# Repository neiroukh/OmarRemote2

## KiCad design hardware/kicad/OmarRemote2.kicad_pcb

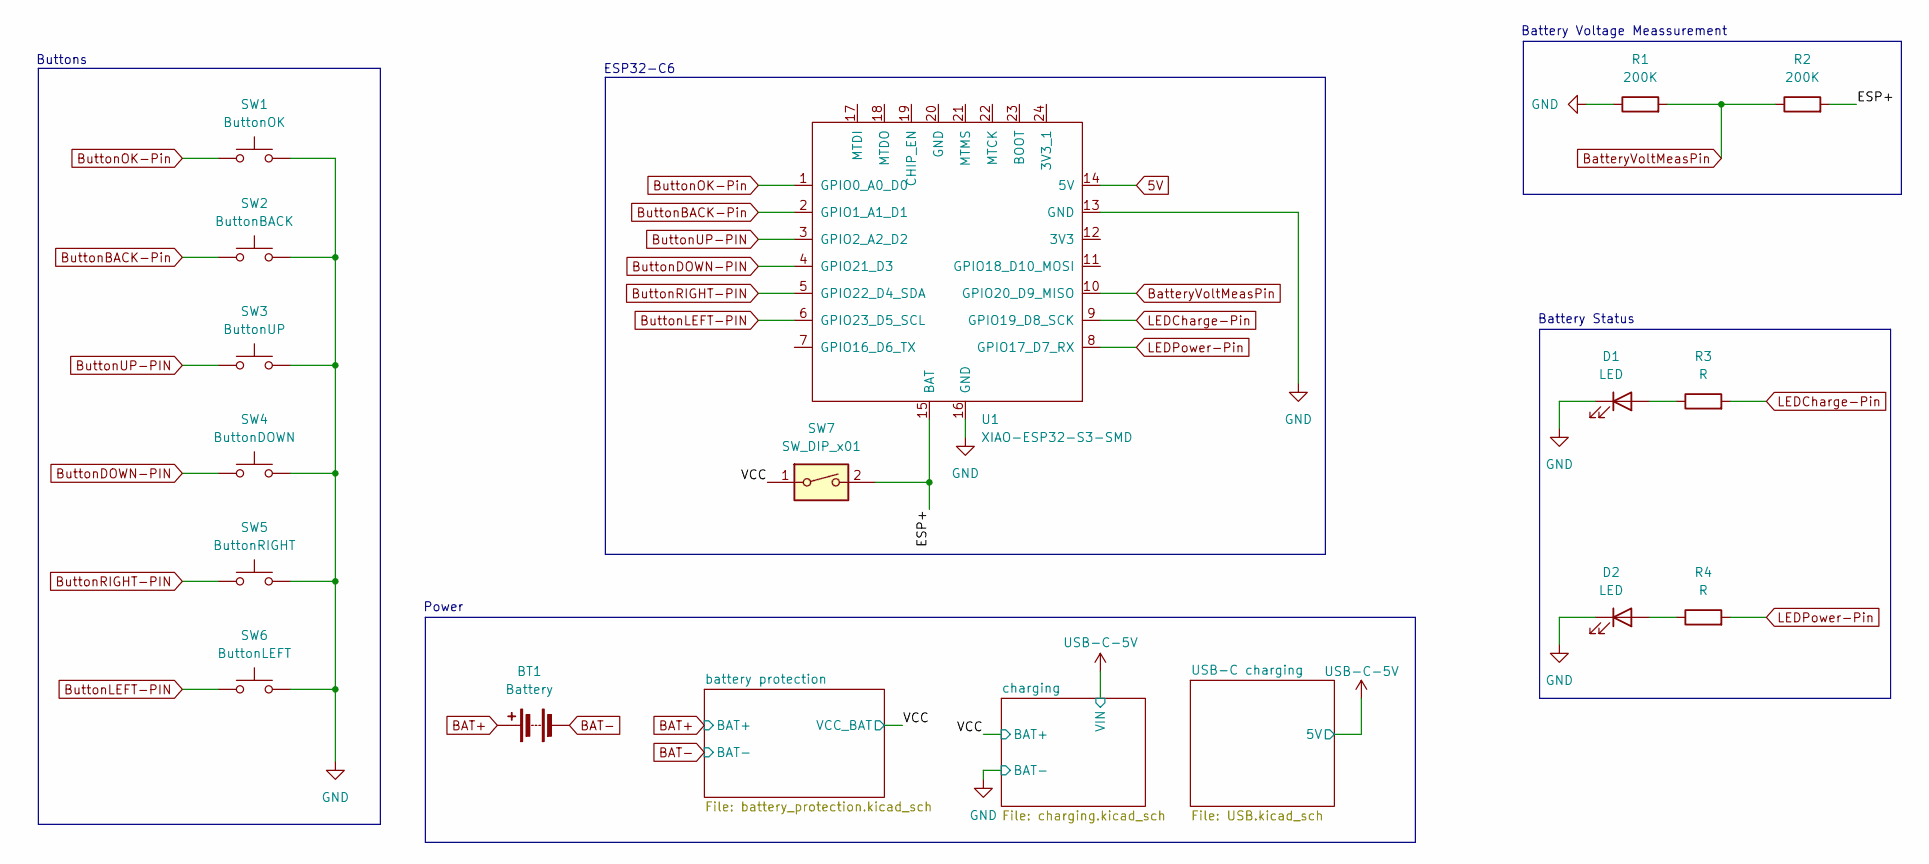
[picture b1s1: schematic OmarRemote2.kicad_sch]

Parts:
BT1: Battery; BatteryHolder_Keystone_1042_1x18650
D1, D2: LED; JST_XH_B2B-XH-A_1x02_P2.50mm_Vertical
R1, R2: 200K; R_0805_2012Metric
R3, R4: R; R_0805_2012Metric
SW1: ButtonOK; SW-TH_4P-L6.0-W6.0-P4.50-LS6.5
SW2: ButtonBACK; SW-TH_4P-L6.0-W6.0-P4.50-LS6.5
SW3: ButtonUP; SW-TH_4P-L6.0-W6.0-P4.50-LS6.5
SW4: ButtonDOWN; SW-TH_4P-L6.0-W6.0-P4.50-LS6.5
SW5: ButtonRIGHT; SW-TH_4P-L6.0-W6.0-P4.50-LS6.5
SW6: ButtonLEFT; SW-TH_4P-L6.0-W6.0-P4.50-LS6.5
SW7: SW_DIP_x01; JST_XH_B2B-XH-AM_1x02_P2.50mm_Vertical
U1: XIAO-ESP32-S3-SMD; XIAO-ESP32C6-SMD

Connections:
5V: U1.14 (5V); also elsewhere on the board
/ESP+: R2.2, SW7.2, U1.15 (BAT)
BAT+: BT1.1 (+), SW7.1; also elsewhere on the board
BAT-: BT1.2 (-); also elsewhere on the board
BatteryVoltMeasPin: R1.2, R2.1, U1.10 (GPIO20_D9_MISO)
ButtonBACK-Pin: SW2.1, U1.2 (GPIO1_A1_D1)
ButtonDOWN-PIN: SW4.1, U1.4 (GPIO21_D3)
ButtonLEFT-PIN: SW6.1, U1.6 (GPIO23_D5_SCL)
ButtonOK-Pin: SW1.1, U1.1 (GPIO0_A0_D0)
ButtonRIGHT-PIN: SW5.1, U1.5 (GPIO22_D4_SDA)
ButtonUP-PIN: SW3.1, U1.3 (GPIO2_A2_D2)
GND: D1.1 (K), D2.1 (K), R1.1, SW1.2, SW2.2, SW3.2, SW4.2, SW5.2, SW6.2, U1.13 (GND), U1.16 (GND); also elsewhere on the board
LEDCharge-Pin: R3.2, U1.9 (GPIO19_D8_SCK)
LEDPower-Pin: R4.2, U1.8 (GPIO17_D7_RX)
unnamed: D1.2 (A), R3.1
unnamed: D2.2 (A), R4.1

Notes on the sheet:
ESP32-C6
Battery Status
Power
Battery Voltage Meassurement
Buttons

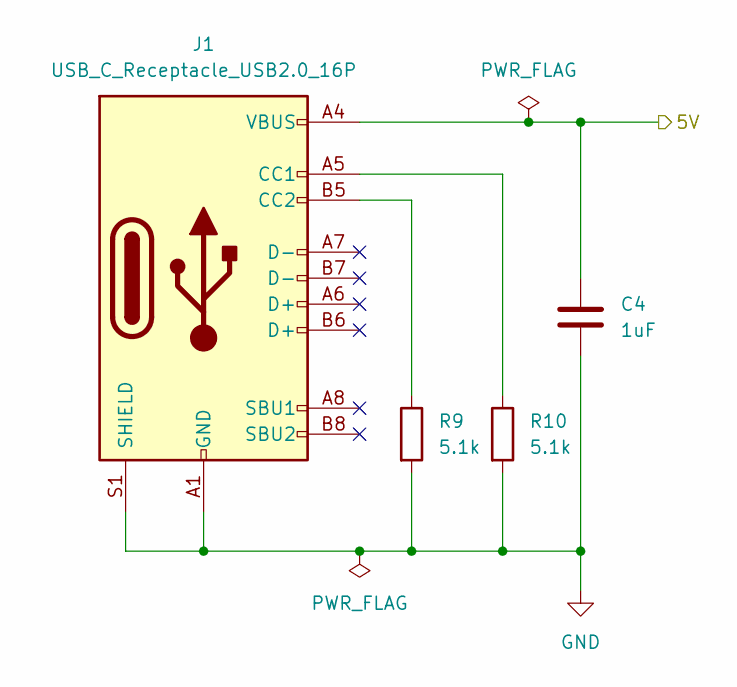
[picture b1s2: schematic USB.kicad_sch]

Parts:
C4: 1uF; C_0603_1608Metric_Pad1.08x0.95mm_HandSolder; LCSC C15849
J1: USB_C_Receptacle_USB2.0_16P; USB_C_Receptacle_G-Switch_GT-USB-7010ASV; LCSC C2988369
R9, R10: 5.1k; R_0603_1608Metric_Pad0.98x0.95mm_HandSolder; LCSC C23186

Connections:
GND: C4.2, J1.A1 (GND), J1.A12 (GND), J1.B1 (GND), J1.B12 (GND), J1.S1 (SHIELD), R9.2, R10.2; also elsewhere on the board
unnamed: J1.A5 (CC1), R10.1
unnamed: J1.B5 (CC2), R9.1
USB-C-5V: C4.1, J1.A4 (VBUS), J1.A9 (VBUS), J1.B4 (VBUS), J1.B9 (VBUS); also elsewhere on the board

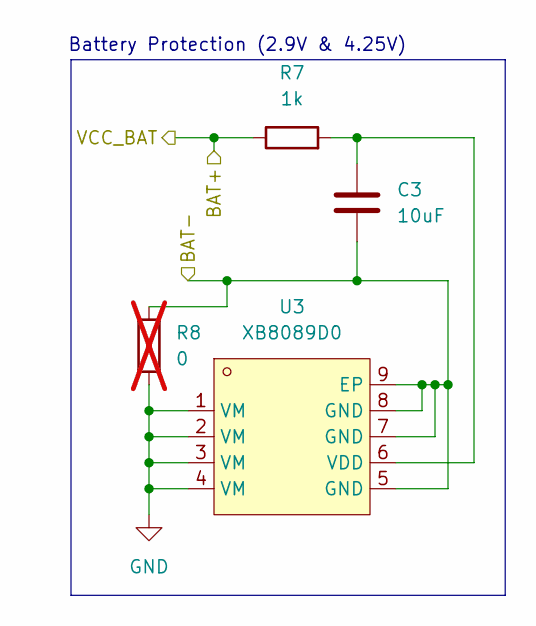
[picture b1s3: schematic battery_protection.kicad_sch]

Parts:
C3: 10uF; C_0603_1608Metric_Pad1.08x0.95mm_HandSolder; LCSC C19702
R7: 1k; R_0603_1608Metric_Pad0.98x0.95mm_HandSolder; LCSC C21190
R8: 0; R_0603_1608Metric_Pad0.98x0.95mm_HandSolder; LCSC C21189; not fitted
U3: XB8089D0; HTSOP-8-1EP_3.9x4.9mm_P1.27mm_EP2.4x3.2mm; LCSC C2760005

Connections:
BAT+: R7.1; also elsewhere on the board
BAT-: C3.2, R8.1, U3.5 (GND), U3.7 (GND), U3.8 (GND), U3.9 (EP); also elsewhere on the board
GND: R8.2, U3.1 (VM), U3.2 (VM), U3.3 (VM), U3.4 (VM); also elsewhere on the board
unnamed: C3.1, R7.2, U3.6 (VDD)

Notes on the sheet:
Battery Protection (2.9V & 4.25V)

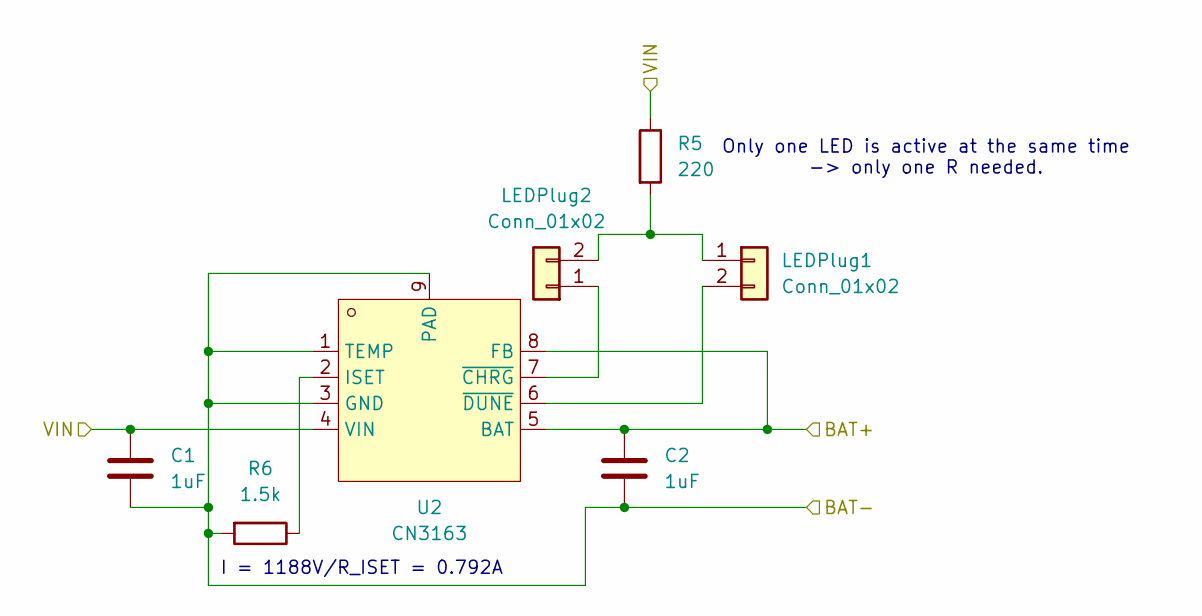
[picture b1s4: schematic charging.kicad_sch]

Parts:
C1, C2: 1uF; C_0603_1608Metric_Pad1.08x0.95mm_HandSolder; LCSC C15849
LEDPlug1, LEDPlug2: Conn_01x02; JST_XH_B2B-XH-A_1x02_P2.50mm_Vertical
R5: 220; R_0603_1608Metric_Pad0.98x0.95mm_HandSolder; LCSC C21190
R6: 1.5k; R_0603_1608Metric_Pad0.98x0.95mm_HandSolder
U2: CN3163; ESOP-8_L4.9-W3.9-P1.27-LS6.0-BL-EP; LCSC Part C559031

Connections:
BAT+: C2.1, U2.5 (BAT), U2.8 (FB); also elsewhere on the board
GND: C1.2, C2.2, R6.2, U2.1 (TEMP), U2.3 (GND), U2.9 (PAD); also elsewhere on the board
unnamed: LEDPlug1.1, LEDPlug2.2, R5.2
unnamed: LEDPlug1.2, U2.6 (~DUNE)
unnamed: LEDPlug2.1, U2.7 (~CHRG)
unnamed: R6.1, U2.2 (ISET)
USB-C-5V: C1.1, R5.1, U2.4 (VIN); also elsewhere on the board

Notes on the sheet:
Only one LED is active at the same time -> only one R needed.
I = 1188V/R_ISET = 0.792A

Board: 2 copper layers, 31 parts (0 on the bottom side), 24 nets, no tracks yet.

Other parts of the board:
J2: Conn_01x03; JST_XH_B3B-XH-A_1x03_P2.50mm_Vertical

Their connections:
5V: J2.2; also elsewhere on the board
GND: J2.3; also elsewhere on the board

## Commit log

2026-02-28 chore: update main gitignore
2026-03-02 feat: add basic KiCad schematic
2026-03-02 feat: add IR-Sender
2026-03-02 feat: add battery charger to schematic
2026-03-02 start work on TP4056 footprint
2026-03-03 further work on TP4056 footprint
2026-03-03 update libaries
2026-03-03 steal subsheets from @MayNiklas
2026-03-03 add switch
2026-03-03 fix voltage measurement
2026-03-04 start work on pcb layout
2026-03-04 firmware init
2026-05-17 update sch to exclude IR
